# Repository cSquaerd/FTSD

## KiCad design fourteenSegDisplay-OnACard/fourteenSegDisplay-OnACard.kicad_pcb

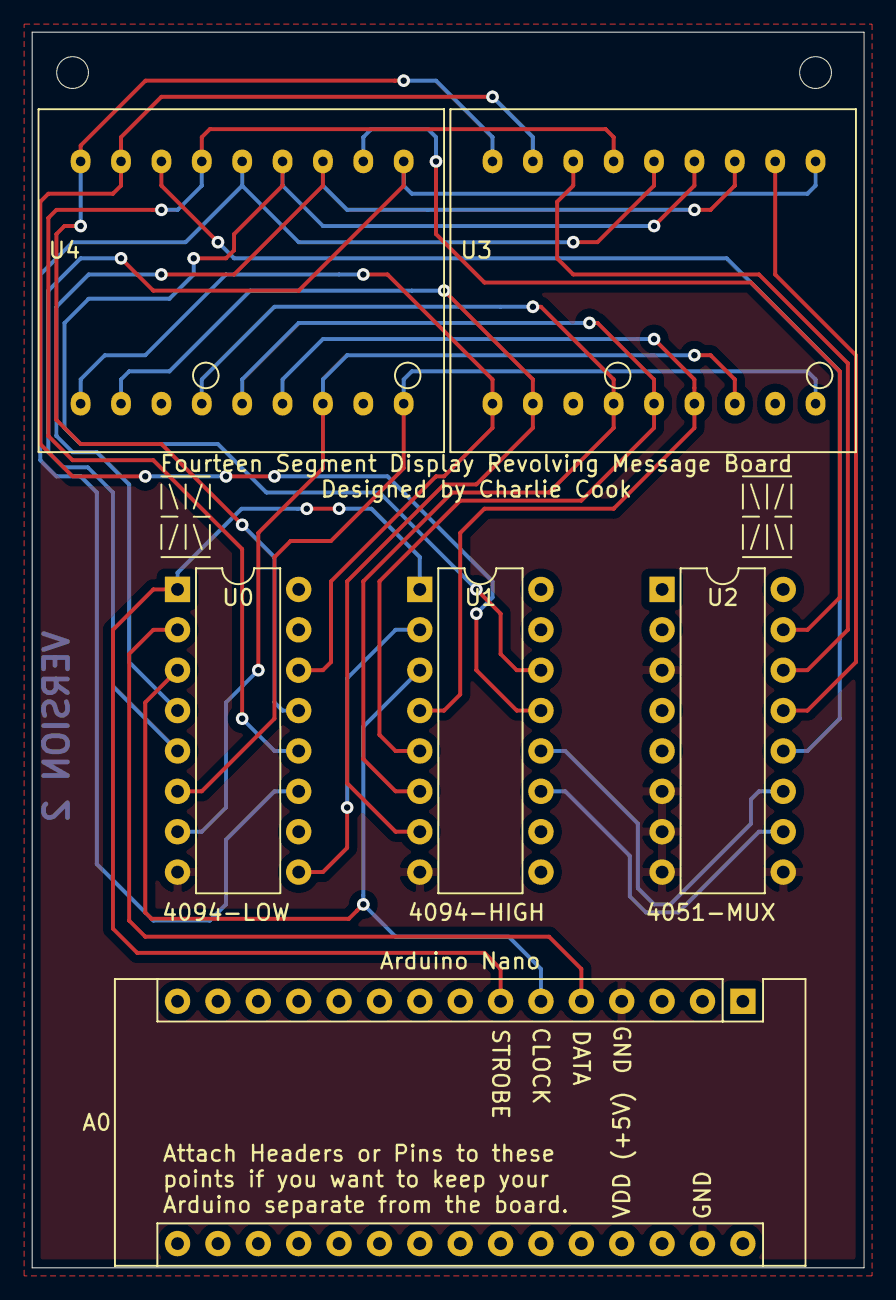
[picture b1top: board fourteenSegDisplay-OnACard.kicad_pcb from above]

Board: 2 copper layers, 52.3 x 77.7 mm, 6 parts (0 on the bottom side), 26 nets.

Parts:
A0: Arduino_Nano_v3.x; Arduino_Nano
U0, U1: 4094; DIP-16_W7.62mm
U2: 4051; DIP-16_W7.62mm
U3, U4: LTP-3784

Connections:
+5V: A0.27, U0.15, U0.16, U1.15, U1.16, U2.16
GND: A0.4, A0.29, U0.8, U1.8, U2.3, U2.6, U2.7, U2.8, U2.9
unnamed: A0.5, U0.2
unnamed: A0.6, U0.3, U1.3
unnamed: A0.7, U0.1, U1.1
unnamed: U0.4, U3.12, U4.12
unnamed: U0.5, U3.10, U4.10
unnamed: U0.6, U3.9, U4.9
unnamed: U0.7, U3.7, U4.7
unnamed: U0.9, U1.2
unnamed: U0.11, U3.14, U4.14
unnamed: U0.12, U3.15, U4.15
unnamed: U0.13, U3.18, U4.18
unnamed: U0.14, U3.1, U4.1
unnamed: U1.4, U3.6, U4.6
unnamed: U1.5, U3.5, U4.5
unnamed: U1.6, U3.4, U4.4
unnamed: U1.7, U3.2, U4.2
unnamed: U1.11, U2.10
unnamed: U1.12, U2.11
unnamed: U1.13, U3.17, U4.17
unnamed: U1.14, U3.13, U4.13
unnamed: U2.12, U4.16
unnamed: U2.13, U3.11
unnamed: U2.14, U3.16
unnamed: U2.15, U4.11

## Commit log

2019-08-04 Added punctuation and symbols to the translate function.
2020-02-25 Updated stuff
2020-05-05 Added PCB KiCAD files
